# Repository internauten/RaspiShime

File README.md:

<!-- cspell:locale en,de-CH -->

# OnOff SHIM für Raspberry PI

[-informational)](#gerber-dateien-für-die-fertigung)

Dies ist ein Versuch das OnOff SHIME von Pimoroni nach zu bauen.

> [!WARNING]  
> Diese Module wurden noch nicht getestet!

Die meisten Artefakte wurden mittels AI (Anthropic Sonnet 5.5) generiert und nur dort manuell angepasst wo die AI scheiterte.

## Funktionsweise

- Taster um den On or Off Vorgang zu initialisieren
- LED die leuchtet im On Zustand und nicht leuchtet im Off Zustand. Während des ShutDown soll sie blinken.
- USB C eingang
- Signale und Strom zum Raspberry PI über GPIO
- Eine Variante soll auch für Raspberry PI 5 taugen bis 5A

## Links

- Link zum Produkt: <https://shop.pimoroni.com/en-ch/products/onoff-shim?variant=41102600138>
- Pinout: <https://pinout.xyz/pinout/onoff_shim>
- Weitere Informationen: <https://retropie.org.uk/forum/topic/15727/tutorial-onoff-shim-exposed-neat-powerswitch-from-pimoroni>
- Die Software ist hier erreichbar: <https://get.pimoroni.com/onoffshim>

## Umsetzung

Der Schaltungsvorschlag deckt die Funktionen aus der Liste ab: Taster Ein/Aus, LED mit Blinken beim Shutdown, USB-C-Eingang, Versorgung über GPIO und bis 9.2 W für den Pi 5.

Die GPIO-Belegung stammt aus der Erinnerung an das Pimoroni-Original. Sie ist vor einer Platinenbestellung gegen das [Pinout](https://pinout.xyz/pinout/onoff_shim) zu prüfen.

### Prinzip

Ein P-MOSFET (Q1) schaltet die 5 V als High-Side-Schalter. Ein Taster zieht dessen Gate kurz auf Masse und schaltet den Pi damit ein. Sobald der Pi läuft, hält er den Schalter über GPIO4 und Q2 selbst fest (Selbsthaltung). Am Ende des Shutdowns lässt GPIO4 los und der Strom ist weg. Derselbe Taster löst per GPIO17 den Shutdown aus.

### Schaltplan

```text
USB-C                                                  Pi GPIO
 VBUS ──[F1 PTC 2.5A]──┬──[TVS SMBJ5.0A]── GND
                       │
                       ├── C_in 100µF/10V ── GND
                       │
                       ├────────────┬───────────────┐
                       │            │               │
                       │          R1 100k        C1 47µF
                       │            │               │
                       │            ├───────────────┘
                       │            │  (= Gate Q1)
                       │         D1 BAT54 (Anode am Gate)
                       │            │         │
                       │            │       Kathode ── Knoten A
                       │            │                   │
                       S            G                   ├── SW1 Taster ── GND
                      Q1 AO3401A (P-MOSFET)             │
                       D                                └── D2 BAT54 (Kathode an A,
                       │                                    Anode an GPIO17 = Pin 11)
                       │
                       ├── 5V_SW ──────────────────────────► Pin 2 + Pin 4 (5V)
                       ├── C_out 100µF ── GND
                       │
                       └── R_LED 1k ──┬── LED (grün) ── GND
                                      │
                                    Q3 D (2N7002, schliesst LED kurz)
                                      │ G ── R4 100k ── GND
                                      │ G ◄──────────── R5 1k ◄── GPIO27 (Pin 13)
                                    Q3 S ── GND

Selbsthaltung:
   Gate Q1 ── Drain Q2 (2N7002), Source Q2 ── GND
   Gate Q2 ◄── R2 1k ◄── GPIO4 (Pin 7)
   Gate Q2 ── R3 100k ── GND

GND USB-C ───────────────────────────────────────────────► Pin 6/9/14 (GND)
CC1, CC2 ── je 5.1k ── GND   (damit liefert das Netzteil 5 V)
```

### Funktionsablauf

| Zustand | Was passiert |
| --- | --- |
| Aus | R1 hält das Gate auf VBUS, Q1 sperrt. Der Pi ist stromlos. |
| Taster drücken | D1 zieht das Gate über den Taster nach GND, Q1 schaltet durch und der Pi bootet. |
| Taster loslassen | C1 und R1 halten das Gate etwa 7 s unten. In dieser Zeit setzt der Pi GPIO4 auf High, Q2 übernimmt die Selbsthaltung. |
| Betrieb, Taster drücken | D2 gibt GPIO17 nach Low, `gpio-shutdown` fährt den Pi herunter. |
| Shutdown fertig | `gpio-poweroff` setzt GPIO4 auf Low, Q2 sperrt, Q1 sperrt und der Strom ist weg. |
| LED | Sie leuchtet, sobald 5V_SW anliegt. Q3 schliesst sie kurz, sodass GPIO27 sie ausschalten oder blinken lassen kann. |

D2 ist nötig. Ohne D2 würde der 3.3-V-Pullup von GPIO17 über D1 das Gate auf etwa 3.6 V ziehen und Q1 teilweise einschalten.

### Software

Einträge in `/boot/firmware/config.txt`:

```ini
dtoverlay=gpio-shutdown,gpio_pin=17,active_low=1,gpio_pull=up
dtoverlay=gpio-poweroff,gpiopin=4,active_low=1
dtoverlay=gpio-led,gpio=27,label=shutdown-led,trigger=default-off
```

Zum Blinken während des Shutdowns ist ein kleiner systemd-Service nötig. Er setzt beim Shutdown `echo timer > /sys/class/leds/shutdown-led/trigger`.

### Hinweise

- **Pi 5:** Bei 9.2 W fliessen etwa 1.85 A bei 5 V. Q1 (AO3401A, ca. 50 mΩ) und der 2.5-A-PTC reichen dafür. Es sind breite Leiterbahnen oder Kupferflächen und mindestens 1 oz Kupfer zu verwenden. Der Pi 5 meldet beim Booten eventuell "Netzteil liefert keine 5 A". Das lässt sich mit `PSU_MAX_CURRENT=5000` in der EEPROM-Konfiguration übergehen.
- **Boot-Zeit:** Braucht der Pi länger als 7 s bis GPIO4, sind C1 oder R1 zu erhöhen.
- **Verbesserungen:** Möglich ist ein USB-C-Stecker mit Power-only-Pins (16-pol.). Ein Load-Switch-IC wie TPS2553 anstelle von PTC und Q1 wäre robuster, ist aber komplizierter.

## KiCad-Umsetzung

Das KiCad-Projekt liegt in [kicad/](kicad/) und wird mit `RaspiShime.kicad_pro` geöffnet.

### Stand

Geprüft wurde bisher nur mit `kicad-cli`: Der Schaltplan hat im ERC 0 Verstösse, und die exportierte Netzliste stimmt mit dem Entwurf überein. Die Schaltplanseite wurde als PDF gerendert und optisch kontrolliert, die Platine als 3D-Bild.

- **Schaltplan** ([RaspiShime.kicad_sch](kicad/RaspiShime.kicad_sch)): A3-Blatt mit allen Bauteilen aus dem Entwurf (USB-C, PTC, TVS, Q1 bis Q3, Taster, LED, 40-Pin-Header). Die Verbindungen laufen über Netz-Labels statt über gezogene Leitungen, deshalb wirkt der Plan etwas ungewohnt. Die `config.txt`-Zeilen stehen als Text im Plan.
- **Platine** ([RaspiShime.kicad_pcb](kicad/RaspiShime.kicad_pcb)): 65 × 42 mm mit Umriss, platzierten Footprints und zugewiesenen Netzen. Auf `F.Cu` und `B.Cu` liegt je eine GND-Fläche über den ganzen Umriss. Der DRC meldet noch 29 offene, nicht geroutete Verbindungen und 4 Wärmefallen mit zu wenig Anbindung, bis Bahnen und Stitching-Vias gesetzt sind.

**Externer Taster:** `J3` (zwei Pads, Footprint `PinHeader_1x02_P2.54mm_Vertical`) liegt parallel zu SW1 an BTN_A und GND. Ein externer Schliesser (Taster mit Arbeitskontakt) hat damit dieselbe Funktion wie SW1 (Einschalten und Shutdown). Bei langen Leitungen sind Störungen und ESD am Eingang möglich, kurze oder geschirmte Leitungen sind vorzuziehen.

Änderungen im Schaltplan werden über *Tools → Update PCB from Schematic* in die Platine übernommen. Die Footprints sind mit den Schaltplan-Symbolen verknüpft.

### Offene Punkte

- **Routing:** Die Platine ist nur platziert. Die 5V-Pfade (VBUS, 5V_SW) brauchen breite Leiterbahnen oder Kupferflächen, bei 2 A etwa 1 mm oder mehr. Die GND-Flächen sind angelegt, aber noch ohne Stitching-Vias, die beide Lagen verbinden. Zusätzlich fehlen Vias unter dem Exposed Pad und in der Nähe von Q1, PTC, Elkos und Header. Nach dem Routen sind die Zonen neu zu füllen (Taste `B`).
- **Platinenform:** Umriss und Platzierung sind eine grobe Annahme. Die Form des Pimoroni-SHIM und Montagelöcher sind nicht nachgebaut.
- **GPIO-Belegung:** GPIO4, 17 und 27 stammen aus der Erinnerung und sind gegen das [Pinout](https://pinout.xyz/pinout/onoff_shim) zu prüfen.
- **Footprints:** Der Header nutzt den Male-Header `PinHeader_2x20`. Ob Stift- oder Buchsenleiste passt, hängt vom Aufbau ab. Der Taster ist ein `SW_SPST_PTS810`, die Dioden sind `BAT54WS` in SOD-323 und der USB-C-Stecker ist ein GCT `USB4105`. Das sind Vorschläge.

## KiCad-Umsetzung 5A

Die zweite Variante liegt in [kicad5A/](kicad5A/) und wird mit `RaspiShime5A.kicad_pro` geöffnet. Sie ist für 5 V bei 5 A (25 W) ausgelegt, also für den Pi 5 mit voller Leistung. Das Prinzip mit Taster, Selbsthaltung, LED und Shutdown-Signal ist unverändert.

### Unterschiede zur 3-A-Variante

| Bereich | 3 A ([kicad/](kicad/)) | 5 A ([kicad5A/](kicad5A/)) |
|---|---|---|
| USB-C | 16-poliger Stecker, 5.1 kΩ an CC1/CC2 (Netzteil liefert höchstens 3 A) | 6-poliger Power-only-Stecker, CC1/CC2 an einen PD-Controller |
| Leistungsaushandlung | keine | STUSB4500 fordert 5 V/5 A per USB-PD an |
| Sicherung | PTC 2.5 A | PTC 6 A (Haltestrom), Bauform 2920 |
| Hauptschalter Q1 | AO3401A (SOT-23, ca. 50 mΩ) | DMP3013SFV (PowerDI3333, ca. 10 bis 13 mΩ) |
| Kondensatoren | 100 µF am Ausgang | 220 µF und 22 µF am Ausgang, 10 µF am Eingang |
| Platine | 65 × 42 mm, Netzklasse `Power3A` mit 1.5 mm Leiterbahnbreite für VBUS_RAW, VBUS und 5V_SW | 65 × 52 mm, Netzklasse `Power5A` mit 2 mm Leiterbahnbreite für VBUS_RAW, VBUS und 5V_SW |

Der STUSB4500 wird direkt aus VBUS versorgt (VDD, VSYS an GND). Seine Ausgänge VBUS_EN_SNK, ATTACH, POWER_OK2/3, GPIO und ALERT bleiben unbenutzt, weil Q1 den Strompfad schaltet. I2C (SDA/SCL) liegt auf den Pi-Pins 3 und 5, damit sich der Chip vom Pi aus programmieren lässt.

### STUSB4500 programmieren (zwingend vor dem ersten Einsatz)

Laut Datenblatt (DS12499, Tabelle 16) verhandelt der STUSB4500 ab Werk bis zu 3 Profile bis 20 V (Standard: PDO2 15 V, PDO3 20 V). An einem PD-Netzteil würde der Pi dann mit bis zu 20 V versorgt und zerstört. Der Chip muss deshalb per I2C im NVM konfiguriert werden:

- `SNK_PDO_NUMB` = 1 (nur PDO1, fest 5 V)
- Strom von PDO1 = 5 A

Ablauf:

1. Beim ersten Einschalten nur ein einfaches 5-V-Netzteil ohne PD verwenden, zum Beispiel ein USB-A-auf-USB-C-Kabel an einem normalen Ladegerät.
2. Taster drücken, der Pi bootet. Der Chip ist über VBUS versorgt und per I2C (Bus 1, GPIO2/3) erreichbar.
3. NVM schreiben, zum Beispiel mit einer STUSB4500-Bibliothek für Python oder Arduino, und mit Aus- und Einschalten prüfen.
4. Erst danach ein PD-Netzteil anschliessen.

Findet der Chip beim Netzteil kein Profil mit 5 V und 5 A, bleibt es laut Datenblatt bei einem Vertrag über 5 V mit dem Strom, den das Netzteil anbietet (zum Beispiel 3 A). Die Schaltung läuft dann, liefert aber nur diesen Strom.

### Voraussetzungen und Grenzen

- **Netzteil und Kabel:** Für 5 V/5 A braucht es ein Netzteil mit 5-V/5-A-Profil (wie das offizielle 27-W-Netzteil des Pi 5) und ein e-marked Kabel für 5 A.
- **Stecker:** Die Strombelastbarkeit des gewählten Steckers (GCT USB4125, 6-polig) ist vor der Bestellung im Datenblatt zu prüfen. Nicht jeder USB-C-Stecker ist für 5 A Dauerstrom ausgelegt.
- **GPIO-Header:** Die 5 V gehen nur über die Pins 2 und 4 zum Pi, bei 5 A also etwa 2.5 A pro Pin. Das liegt nahe am üblichen Grenzwert von Stiftleisten (etwa 3 A pro Pin).
- **Leiterbahnen:** Für 5 A sind breite Leiterbahnen (2 mm oder mehr) oder Kupferflächen auf beiden Lagen und 2 oz Kupfer sinnvoll. Im Platinenaufbau der 5-A-Platine sind 2 oz (0.07 mm) für beide Kupferlagen eingetragen (Dielektrikum 1.46 mm, Gesamtdicke 1.6 mm). Das dokumentiert die Wahl nur, das Kupfergewicht ist bei der Bestellung beim Hersteller zusätzlich auszuwählen. Unter Q1 und dem PTC ist Kupferfläche zur Wärmeabfuhr nötig. Die Verlustleistung von PTC und Q1 beträgt zusammen grob 0.7 W.
- **Pi-Konfiguration:** Der Pi bekommt über GPIO keine PD-Information. Für die volle Leistung ist in der EEPROM-Konfiguration `PSU_MAX_CURRENT=5000` zu setzen. Für USB-Geräte mit hohem Strombedarf kann zusätzlich `usb_max_current_enable=1` in der `config.txt` nötig sein.

### Stand

Geprüft wurde nur mit `kicad-cli`: Der Schaltplan hat im ERC 0 Verstösse, die Netzliste stimmt mit dem Entwurf überein, und der DRC meldet noch 51 offene, nicht geroutete Verbindungen und 2 Wärmefallen mit zu wenig Anbindung. Auf `F.Cu` und `B.Cu` liegt je eine GND-Fläche über den ganzen Umriss. Die Schaltplanseite wurde als PDF gerendert und optisch kontrolliert, die Platine als 3D-Bild. Die Schaltung wurde nicht aufgebaut oder getestet.

**Externer Taster:** Wie bei der 3-A-Variante liegt `J3` (zwei Pads, `PinHeader_1x02_P2.54mm_Vertical`) parallel zu SW1 an BTN_A und GND und ist für einen externen Schliesser gedacht. Bei langen Leitungen sind Störungen und ESD am Eingang möglich.

### Offene Punkte

- **STUSB4500-Beschaltung:** Die Werte stammen aus der Referenzschaltung im Datenblatt (Abschnitt 6.2, Bild 9): 1 µF an VREG_1V2 und VREG_2V7, 470 Ω an VBUS_VS_DISCH, 1 kΩ an DISCH, 100 kΩ nach GND an ADDR0, ADDR1 und RESET. Die Zeichnung im Datenblatt war als Text nur teilweise lesbar. Die genaue Verdrahtung (zum Beispiel VDD direkt an VBUS mit 1 µF) ist deshalb gegen Bild 9 zu prüfen.
- **CC-Schutz:** ESD-Schutz an CC1/CC2 (im Datenblatt ein ESDA25W) ist nicht vorgesehen.
- **Routing und Platine:** Die Platine ist nur platziert. Es gibt weder Leiterbahnen noch Stitching-Vias, die Leistungsnetze (VBUS_RAW, VBUS, 5V_SW) haben keine eigene Fläche, und die Platinenform ist eine grobe Annahme.
- **GPIO-Belegung:** Wie bei der 3-A-Variante gegen das [Pinout](https://pinout.xyz/pinout/onoff_shim) zu prüfen.

## Mechanischer Aufbau mit Buchsenleiste

Statt einer Stiftleiste kann an der Unterseite eine 2×20-Buchsenleiste mit extra langen Pins (Stacking-Header) sitzen. Die Buchse steckt dann auf dem Pi, und die langen Pins ragen oben durch die Platine, sodass dort wieder eine Stiftleiste für weitere Platinen oder Kabel zur Verfügung steht.

- **Footprint:** Der Footprint `PinSocket_2x20_P2.54mm_Vertical` ist das Spiegelbild von `PinHeader_2x20_P2.54mm_Vertical` (bei der Buchsenleiste liegt Pin 2 links von Pin 1). Er muss deshalb auf die Unterseite (`B.Cu`) gelegt werden, dann liegen alle Pad-Nummern wieder an denselben Koordinaten wie bei der Stiftleiste und passen zu den Pins am Pi. Auf der Oberseite würde die Belegung gespiegelt. In beiden Platinen (3 A und 5 A) liegt J2 so auf der Unterseite. Die Pad-Koordinaten sind gegenüber der früheren Stiftleiste unverändert.
- **Pinlänge oben:** Die Pins müssen über das höchste Bauteil auf der Oberseite hinausragen, damit eine weitere Platine darüber Platz hat. Das höchste Bauteil sind die Elektrolytkondensatoren (Bauhöhe etwa 5.4 mm, `CP_Elec_6.3x5.4`). Die genaue Pinlänge ist im Datenblatt des gewählten Stacking-Headers zu prüfen.
- **Abstand zum Pi:** Bei einer Buchsenleiste mit üblicher Bauhöhe von etwa 8.5 mm liegt die Platine rund 11 mm über dem Pi. Die Platine deckt den Pi grossflächig ab (65 × 42 mm bei 3 A, 65 × 52 mm bei 5 A). Beim Pi 5 mit Kühler oder aktivem Lüfter kann das zu eng werden. Dann ist ein Header mit höherem Buchsenkörper nötig, oder die Platine bekommt einen Ausschnitt über dem Kühler.
- **Unterseite:** Auf der Unterseite sitzen keine Bauteile. Der Buchsenkörper liegt auf der GND-Fläche von `B.Cu`, das ist unkritisch.
- **Strom:** Die 5 V laufen weiter nur über die Pins 2 und 4. Die Kontakte einer Buchsenleiste sind meist mit etwa 3 A pro Pin angegeben. Das ist bei der 5-A-Variante ein knapper Wert (siehe oben).
- **Rückwirkung:** Über die oberen Pins ist 5V_SW zugänglich. Eine aufgesteckte Platine darf nicht ebenfalls 5 V einspeisen, sonst speisen zwei Quellen dasselbe Netz.
- **3D-Ansicht:** KiCad enthält kein 3D-Modell für eine Buchsenleiste mit durchgehenden langen Stiften (Stacking-Header). Für J2 gibt es deshalb ein eigenes Modell [3d/stacking_header_2x20.step](3d/stacking_header_2x20.step). Es wird mit dem CadQuery-Skript [3d/stacking_header_2x20.py](3d/stacking_header_2x20.py) erzeugt (`python stacking_header_2x20.py 15`, Argument = Stiftlänge über der Platinenoberseite in mm, Standard 15 mm). Das Modell enthält den Buchsenkörper (8.5 mm hoch, schwarz) und 40 durchgehende Stifte (0.64 mm quadratisch, golden). Der Ursprung liegt in der Mitte von Pin 1, Pin 2 bei X = -2.54 mm wie beim Footprint `PinSocket_2x20_P2.54mm_Vertical`. Z = 0 ist die Platinenfläche auf der Bestückungsseite, der Körper liegt bei Z = 0 bis 8.5 mm und wird bei `B.Cu` automatisch nach unten gespiegelt. Die Stifte reichen von Z = 2 mm bis 16.6 mm unter Z = 0 (Platinendicke 1.6 mm plus 15 mm). Beide Platinen binden das Modell bei J2 über `${KIPRJMOD}/../3d/stacking_header_2x20.step` ein und verwenden es anstelle der beiden Standardmodelle. Die Einbindung ist nur in der Platine eingetragen (nicht in der Footprint-Bibliothek) und hat keinen Einfluss auf Netze oder Fertigungsdaten.
- **GPIO-Prüfung (pinout.xyz):** Die Seite nennt für den OnOff SHIM GPIO4 (Pin 7, "Shutdown") und GPIO17 (Pin 11, "Power Button") und gibt "Uses 2 GPIO pins" an. Damit stimmen GPIO4 und GPIO17 mit dieser Umsetzung überein. Die Seite nennt keinen GPIO für die rote LED und keine Signalpolarität. GPIO27 für die LED (Q3, R5) ist deshalb eine eigene Erweiterung dieser Umsetzung und kein Merkmal des Originals. Die Polarität von GPIO4 und GPIO17 ist gegen das Skript von Pimoroni (`get.pimoroni.com/onoffshim`) zu prüfen, bevor die `dtoverlay`-Zeilen in `config.txt` als gesichert gelten.
- **Polaritätsprüfung (Pimoroni-Daemon):** Der Installer `get.pimoroni.com/onoffshim` richtet den Bash-Daemon `cleanshutd` aus dem Repository `pimoroni/clean-shutdown` ein und schreibt nichts in `config.txt`. `setup.sh` setzt für den OnOff SHIM `trigger_pin 17`, `poweroff_pin 4`, `led_pin 17`, `hold_time 1`. GPIO17 ist ein Eingang mit Pull-up (`raspi-gpio set 17 ip pu`), der gedrückte Taster liest sich als Low (aktiv Low), und der Daemon fährt nach 1 s Low herunter. Dieselbe Leitung dient im Original auch als LED-Ausgang (Blinken). GPIO4 wird beim Ausschalten als Ausgang auf Low gelegt (0.5 s, ohne Pull-Einstellung). Im Ruhezustand liegt GPIO4 durch den Standard-Pull-up auf High. Das passt zu dieser Schaltung: High an GPIO4 hält Q2 durchgeschaltet (Strom bleibt an), Low gibt ihn frei. Die Zeilen `gpio-shutdown,gpio_pin=17,active_low=1,gpio_pull=up` und `gpio-poweroff,gpiopin=4,active_low=1` sind damit polaritätsrichtig. `gpio-poweroff` mit `active_low=1` legt den Pin beim Start auf High und beim Ausschalten auf Low.
- **Unterschiede zum Original:** Das Original wertet GPIO17 erst nach 1 s Low aus. Das Overlay `gpio-shutdown` löst dagegen sofort nach dem Entprellen aus. Ein längeres Halten lässt sich über den Parameter `debounce` (in Millisekunden) nachbilden, zum Beispiel `debounce=1000`, falls das gewünscht ist. Die LED hängt hier an GPIO27 statt an GPIO17, und GPIO17 ist nur ein Eingang.

## Gerber-Dateien für die Fertigung

### Voraussetzungen vor der Ausgabe

- DRC der Platine ohne Fehler und ohne unverbundene Elemente. Stand: 3 A erfüllt dies, 5 A noch nicht (offene Verbindungen).
- ERC des Schaltplans ohne Fehler.
- GPIO-Belegung gegen das Pinout geprüft (siehe Abschnitt "Mechanischer Aufbau mit Buchsenleiste", Punkte zur GPIO-Prüfung).
- Platine in KiCad gespeichert und die Zonen neu gefüllt (Taste `B`), damit die Gerber-Dateien den aktuellen Stand enthalten.

### Ausgabe in KiCad 10

1. Im Platineneditor *Datei → Fertigungsausgaben → Gerber (.gbr)* öffnen und einen Ausgabeordner wählen, zum Beispiel `gerber/`.
2. Lagen: `F.Cu`, `B.Cu`, `F.Paste`, `B.Paste`, `F.Silkscreen`, `B.Silkscreen`, `F.Mask`, `B.Mask`, `Edge.Cuts`.
3. Gerber-X2-Attribute aktiv lassen und keine Protel-Dateiendungen verwenden. Dann *Plot* ausführen.
4. *Bohrdateien erzeugen*: Format Excellon, PTH und NPTH in getrennten Dateien, absolutes Bohrkoordinatensystem.
5. Den Ordner als ZIP-Datei packen und beim Fertiger hochladen.

### Ausgabe per Kommandozeile

Aufruf im jeweiligen Projektordner (`kicad/` oder `kicad5A/`, Dateiname entsprechend `RaspiShime.kicad_pcb` beziehungsweise `RaspiShime5A.kicad_pcb`):

```powershell
& "C:\Program Files\KiCad\10.0\bin\kicad-cli.exe" pcb export gerbers -o gerber/ --layers "F.Cu,B.Cu,F.Paste,B.Paste,F.Silkscreen,B.Silkscreen,F.Mask,B.Mask,Edge.Cuts" RaspiShime.kicad_pcb
& "C:\Program Files\KiCad\10.0\bin\kicad-cli.exe" pcb export drill -o gerber/ --format excellon --generate-map RaspiShime.kicad_pcb
```

`kicad-cli.exe` liegt unter `C:\Program Files\KiCad\10.0\bin`. In PowerShell ist vor einem in Anführungszeichen stehenden Pfad der Aufrufoperator `&` nötig, sonst meldet PowerShell den Fehler "Unerwartetes Token". In der Eingabeaufforderung (`cmd`) und in Git Bash entfällt das `&` (in Git Bash lautet der Pfad `"/c/Program Files/KiCad/10.0/bin/kicad-cli.exe"`).

### Angaben bei der Bestellung

- **Lagen und Dicke:** 2 Lagen, 1.6 mm.
- **Kupfergewicht:** 3 A: Standard (1 oz). 5 A: 2 oz auf beiden Lagen. Das Kupfergewicht steht nicht in den Gerber-Dateien, sondern nur im Bestellformular (die Angabe im Stackup der Platine dient nur der Dokumentation).
- **Oberfläche:** HASL bleifrei oder ENIG. Wegen der feinen Pads des USB-C-Steckers ist ENIG vorzuziehen.
- **Bestückung durch den Fertiger:** Zusätzlich BOM und Bestückungsdaten (*Datei → Fertigungsausgaben → Bestückungsdaten*) erzeugen. Die vorhandenen CSV-Dateien im Projekt sind veraltet (J3 und PinSocket fehlen) und vorher neu zu exportieren.
- **J2:** Die Buchsenleiste mit langen Stiften liegt auf der Unterseite und wird in der Regel von Hand gelötet.

## Lizenz

Das Projekt steht unter der MIT-Lizenz (siehe [LICENSE](LICENSE)). Sie gilt für alle Dateien dieses Repositorys, also auch für die KiCad-Projekte, das CadQuery-Skript und das daraus erzeugte 3D-Modell. Das Urheberrechtsfeld nennt "internauten" als Inhaber. Die Lizenz betrifft nur diese Nachbildung. Entwurf und Marke des Pimoroni OnOff SHIM bleiben beim Hersteller, und die von KiCad verwendeten Bibliotheken (Symbole, Footprints, 3D-Modelle) stehen unter deren eigenen Lizenzen.

Copyright (c) 2026 die.internauten.ch GmbH

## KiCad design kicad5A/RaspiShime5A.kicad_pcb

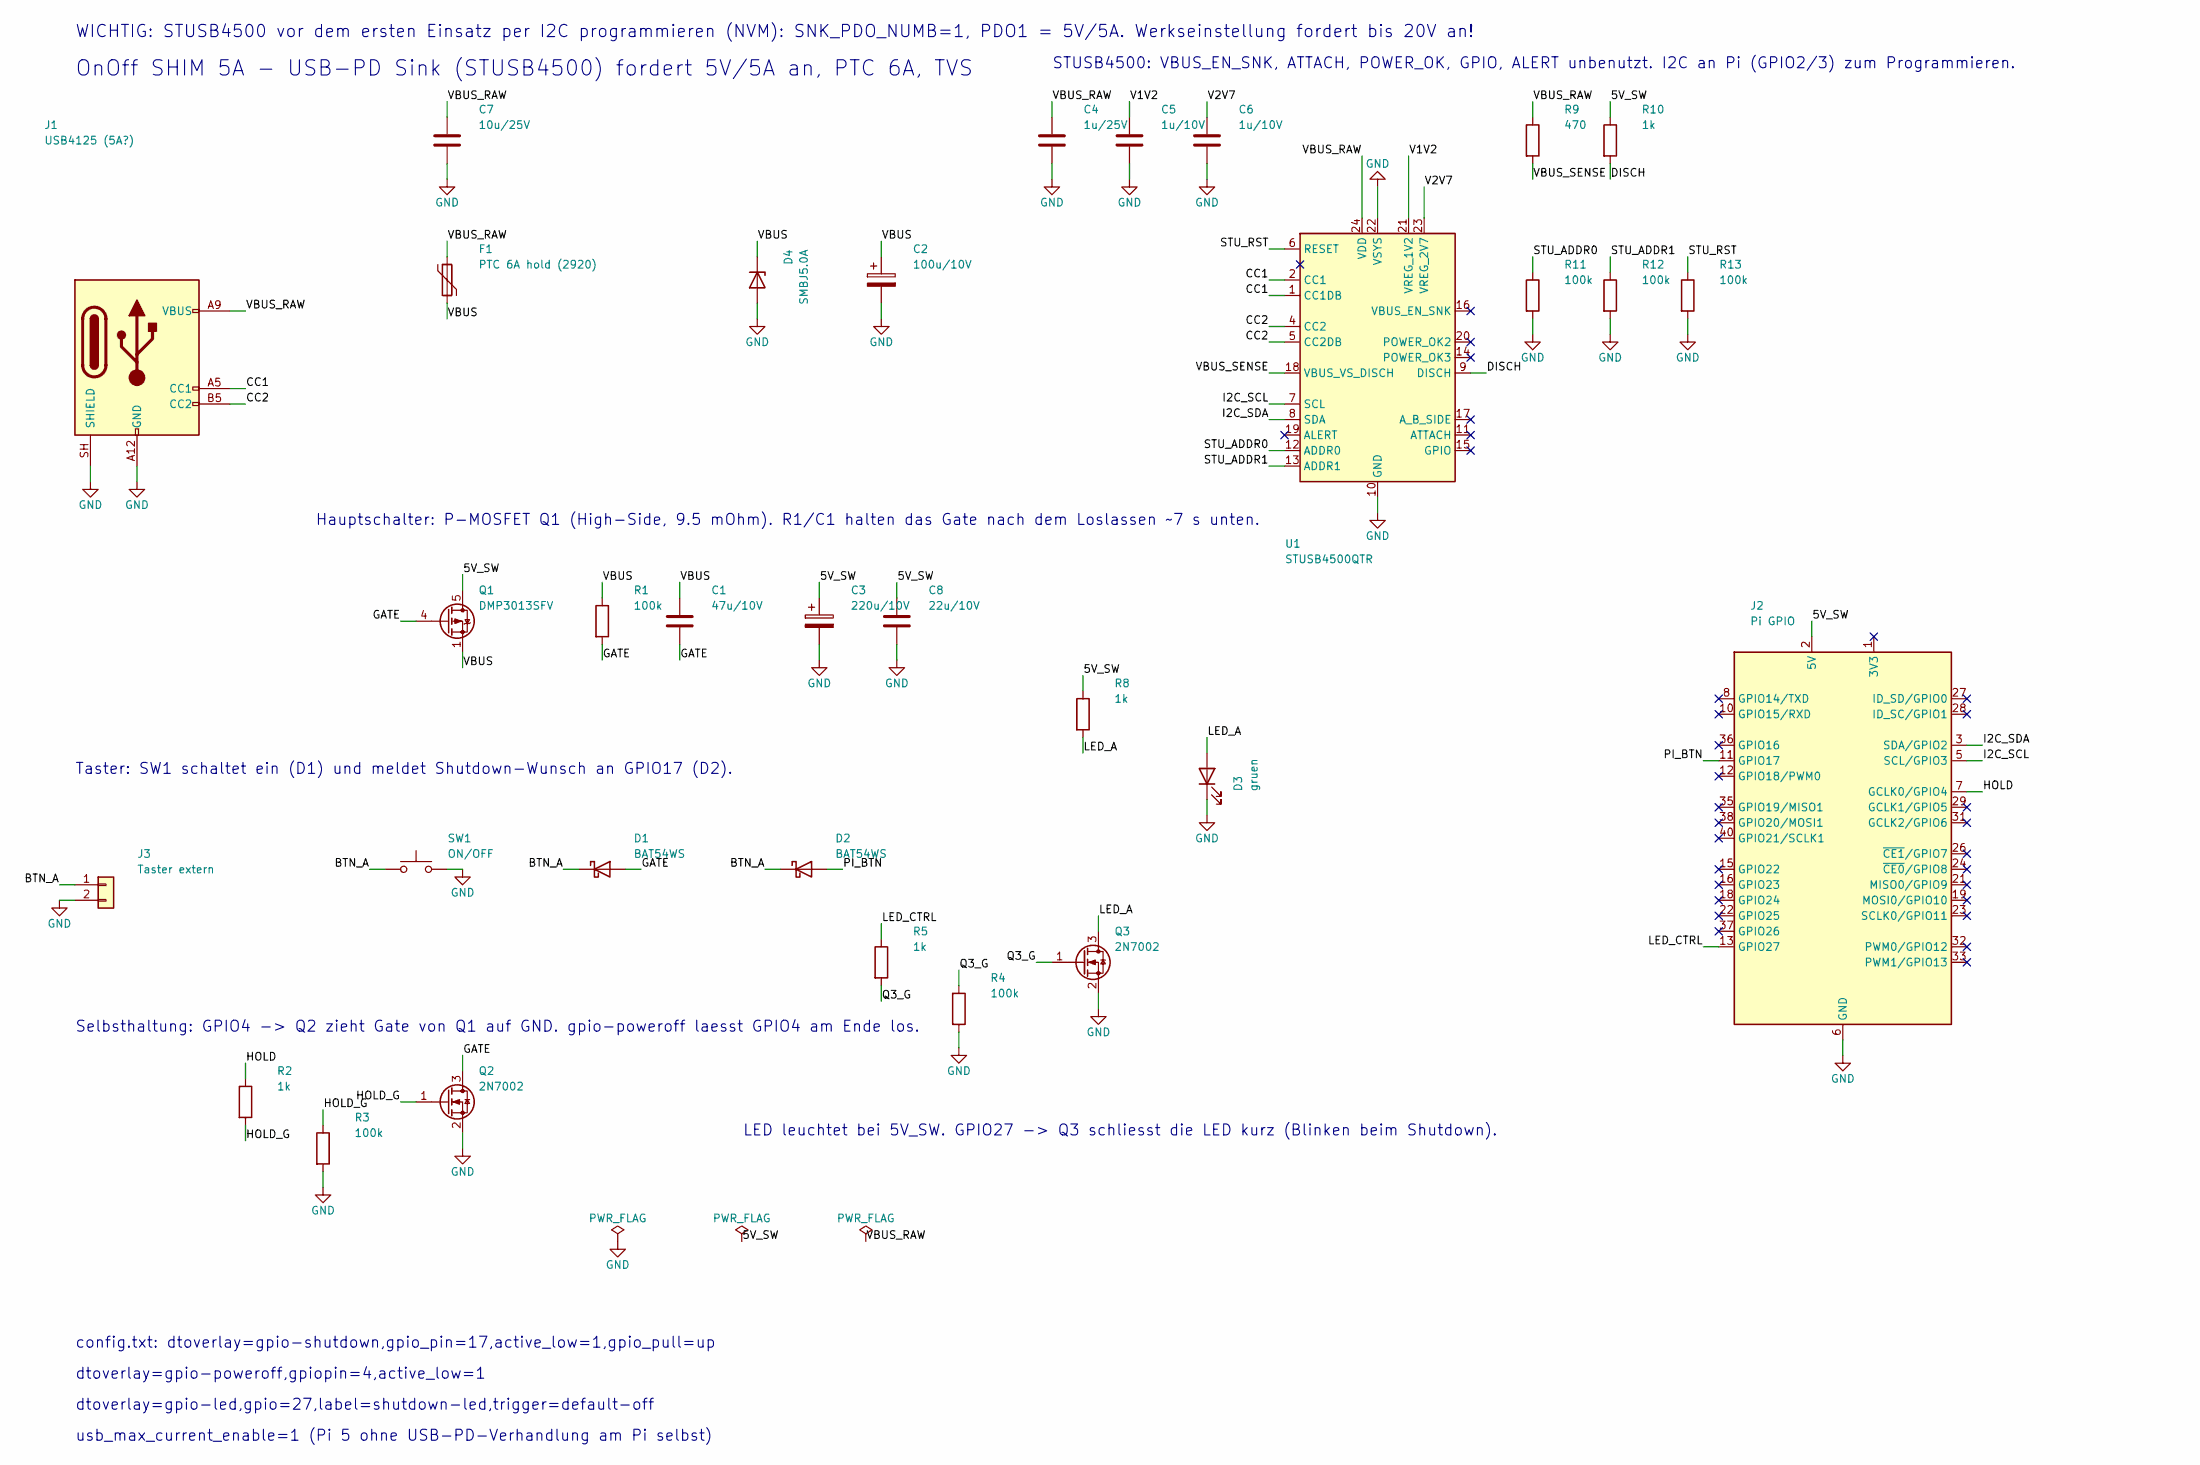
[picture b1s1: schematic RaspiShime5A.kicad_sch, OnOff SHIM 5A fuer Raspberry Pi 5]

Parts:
C1: 47u/10V; C_1210_3225Metric
C2: 100u/10V; CP_Elec_6.3x5.4
C3: 220u/10V; CP_Elec_6.3x5.4
C4: 1u/25V; C_0603_1608Metric
C5, C6: 1u/10V; C_0603_1608Metric
C7: 10u/25V; C_1206_3216Metric
C8: 22u/10V; C_1206_3216Metric
D1, D2: BAT54WS; D_SOD-323
D3: gruen; LED_0603_1608Metric
D4: SMBJ5.0A; D_SMB
F1: PTC 6A hold (2920); Fuse_2920_7451Metric
J1: USB4125 (5A?); USB_C_Receptacle_GCT_USB4125-xx-x_6P_TopMnt_Horizontal
J2: Pi GPIO; PinSocket_2x20_P2.54mm_Vertical
J3: Taster extern; PinHeader_1x02_P2.54mm_Vertical
Q1: DMP3013SFV; Diodes_PowerDI3333-8
Q2, Q3: 2N7002; SOT-23
R1, R3, R4, R11, R12, R13: 100k; R_0603_1608Metric
R2, R5, R8, R10: 1k; R_0603_1608Metric
R9: 470; R_0603_1608Metric
SW1: ON/OFF; SW_SPST_PTS810
U1: STUSB4500QTR; QFN-24-1EP_4x4mm_P0.5mm_EP2.7x2.7mm

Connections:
5V_SW: C3.1, C8.1, J2.2 (5V), J2.4 (5V), Q1.5 (D), R8.1, R10.1
BTN_A: D1.1 (K), D2.1 (K), J3.1, SW1.1
CC1: J1.A5 (CC1), U1.1 (CC1DB), U1.2 (CC1)
CC2: J1.B5 (CC2), U1.4 (CC2), U1.5 (CC2DB)
DISCH: R10.2, U1.9 (DISCH)
GATE: C1.2, D1.2 (A), Q1.4 (G), Q2.3 (D), R1.2
GND: C2.2, C3.2, C4.2, C5.2, C6.2, C7.2, C8.2, D3.1 (K), D4.2 (A), J1.A12 (GND), J1.B12 (GND), J1.SH (SHIELD), J2.6 (GND), J2.9 (GND), J2.14 (GND), J2.20 (GND), J2.25 (GND), J2.30 (GND), J2.34 (GND), J2.39 (GND), J3.2, Q2.2 (S), Q3.2 (S), R3.2, R4.2, R11.2, R12.2, R13.2, SW1.2, U1.10 (GND), U1.22 (VSYS), U1.25 (GND)
HOLD: J2.7 (GCLK0/GPIO4), R2.1
HOLD_G: Q2.1 (G), R2.2, R3.1
I2C_SCL: J2.5 (SCL/GPIO3), U1.7 (SCL)
I2C_SDA: J2.3 (SDA/GPIO2), U1.8 (SDA)
LED_A: D3.2 (A), Q3.3 (D), R8.2
LED_CTRL: J2.13 (GPIO27), R5.1
PI_BTN: D2.2 (A), J2.11 (GPIO17)
Q3_G: Q3.1 (G), R4.1, R5.2
STU_ADDR0: R11.1, U1.12 (ADDR0)
STU_ADDR1: R12.1, U1.13 (ADDR1)
STU_RST: R13.1, U1.6 (RESET)
V1V2: C5.1, U1.21 (VREG_1V2)
V2V7: C6.1, U1.23 (VREG_2V7)
VBUS: C1.1, C2.1, D4.1 (K), F1.2, Q1.1 (S), Q1.2 (S), Q1.3 (S), R1.1
VBUS_RAW: C4.1, C7.1, F1.1, J1.A9 (VBUS), J1.B9 (VBUS), R9.1, U1.24 (VDD)
VBUS_SENSE: R9.2, U1.18 (VBUS_VS_DISCH)

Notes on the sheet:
WICHTIG: STUSB4500 vor dem ersten Einsatz per I2C programmieren (NVM): SNK_PDO_NUMB=1, PDO1 = 5V/5A. Werkseinstellung fordert bis 20V an!
LED leuchtet bei 5V_SW. GPIO27 -> Q3 schliesst die LED kurz (Blinken beim Shutdown).
STUSB4500: VBUS_EN_SNK, ATTACH, POWER_OK, GPIO, ALERT unbenutzt. I2C an Pi (GPIO2/3) zum Programmieren.
dtoverlay=gpio-poweroff,gpiopin=4,active_low=1
usb_max_current_enable=1 (Pi 5 ohne USB-PD-Verhandlung am Pi selbst)
Taster: SW1 schaltet ein (D1) und meldet Shutdown-Wunsch an GPIO17 (D2).
dtoverlay=gpio-led,gpio=27,label=shutdown-led,trigger=default-off
Selbsthaltung: GPIO4 -> Q2 zieht Gate von Q1 auf GND. gpio-poweroff laesst GPIO4 am Ende los.
Hauptschalter: P-MOSFET Q1 (High-Side, 9.5 mOhm). R1/C1 halten das Gate nach dem Loslassen ~7 s unten.
OnOff SHIM 5A - USB-PD Sink (STUSB4500) fordert 5V/5A an, PTC 6A, TVS
config.txt: dtoverlay=gpio-shutdown,gpio_pin=17,active_low=1,gpio_pull=up

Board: 2 copper layers, 32 parts (1 on the bottom side), 23 nets, no tracks yet.
